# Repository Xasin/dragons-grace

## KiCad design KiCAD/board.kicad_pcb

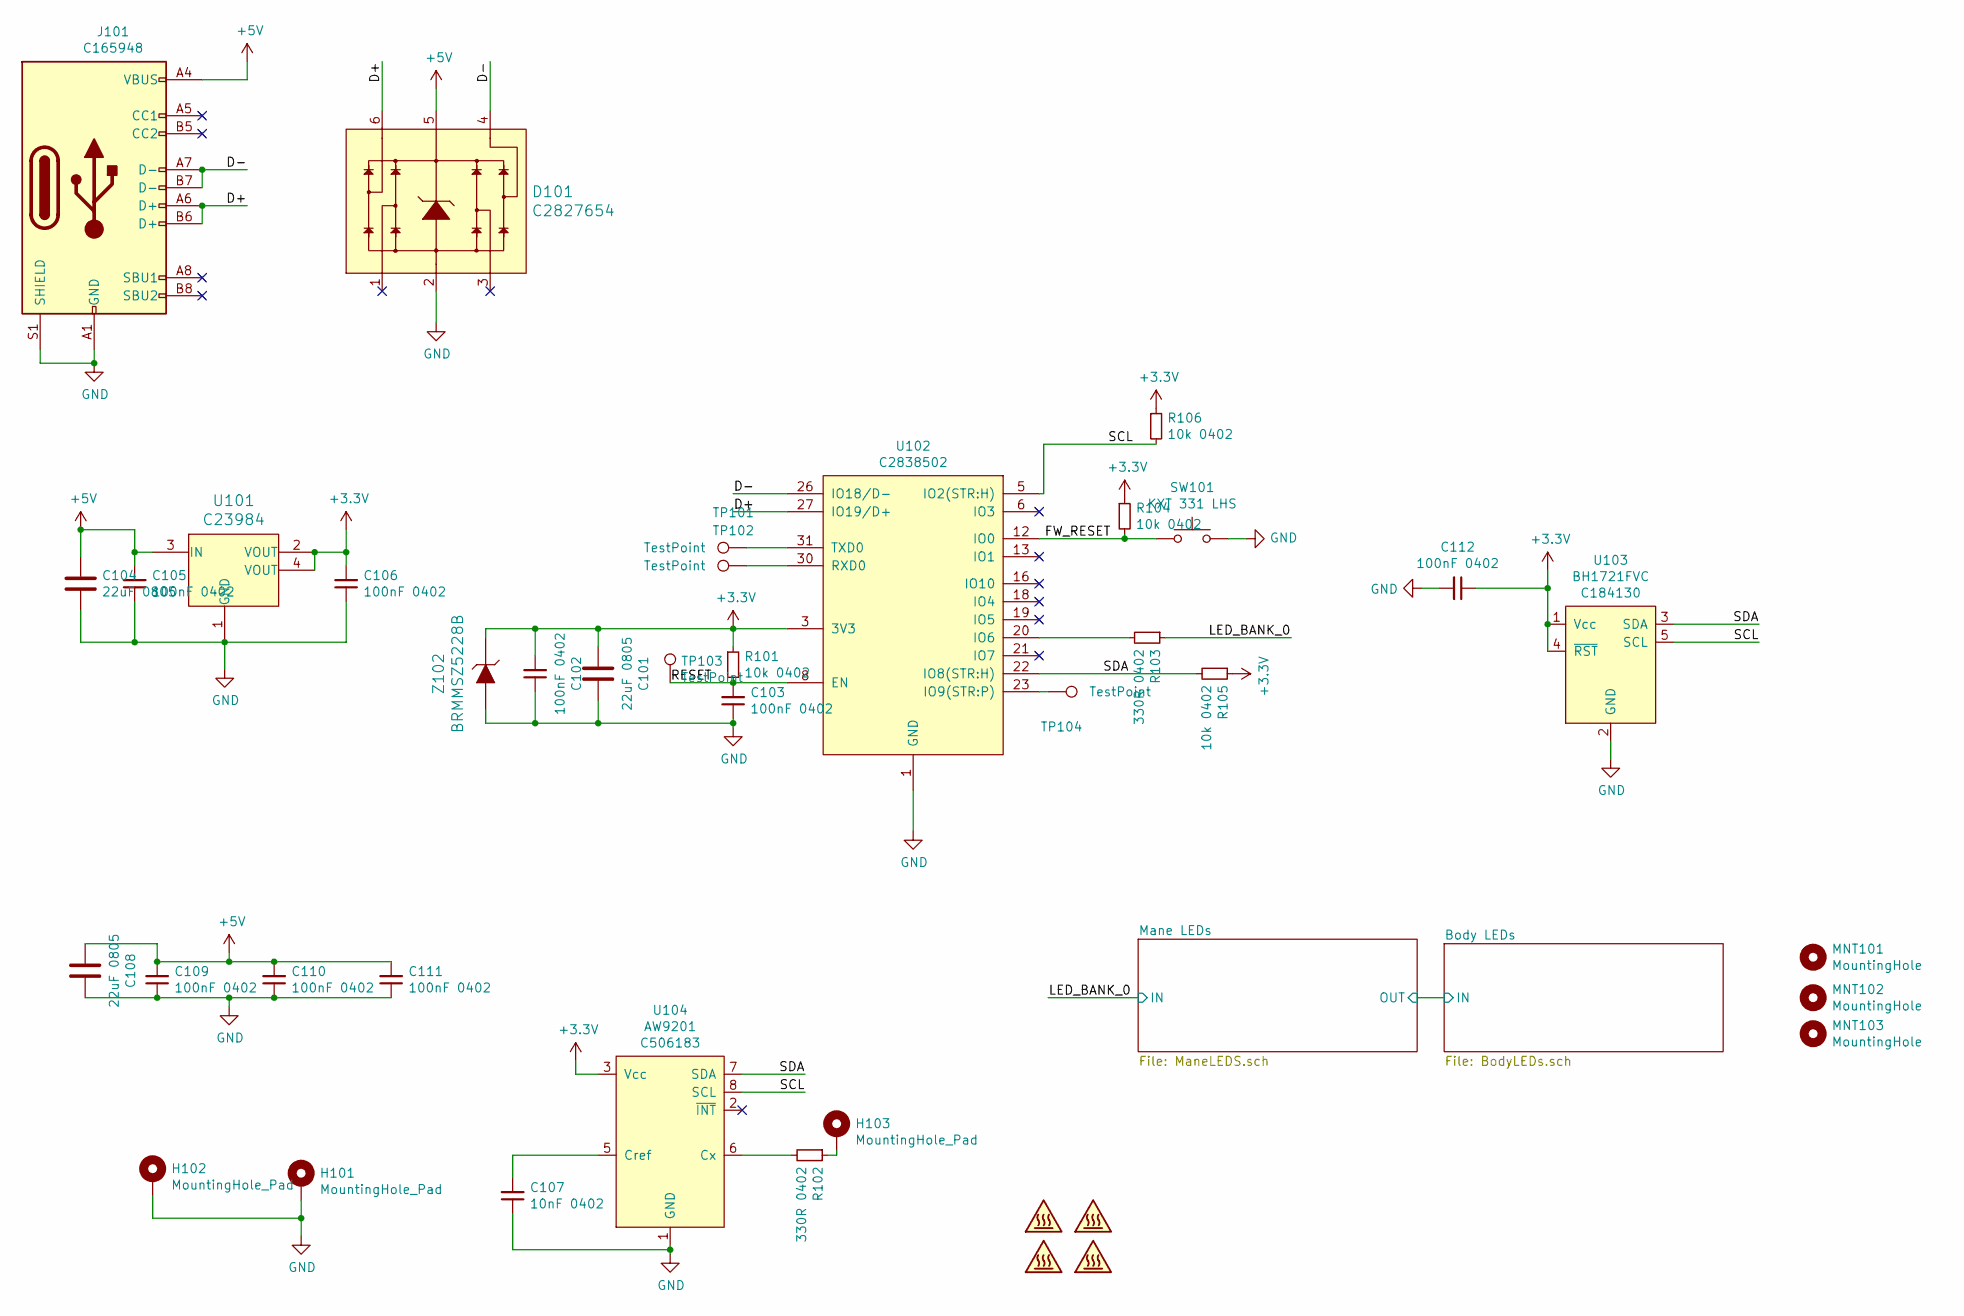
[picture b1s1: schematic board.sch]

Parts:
C101, C104, C108: 22uF 0805; C_0805_2012Metric; JLCPART C45783
C102, C103, C105, C106, C109, C111, C112: 100nF 0402; C_0402_1005Metric; JLCPART C307331
C107: 10nF 0402; C_0402_1005Metric
C110: 100nF 0402; C_0402_1005Metric
D101: C2827654; SOT23-6L; MPN USBLC6-2SC6; Digi-Key_PN 497-5235-1-ND
H101, H102, H103: MountingHole_Pad; MountingHole_1.5mm_M1_Pad_Via
J101: C165948; USB_C_Receptacle_HRO_TYPE-C-31-M-12; JLCPART C165948
MNT101, MNT102, MNT103: MountingHole; JLC_TOOLINGHOLE
R101, R104, R105, R106: 10k 0402; R_0402_1005Metric; JLCPART C25744
R102, R103: 330R 0402; R_0402_1005Metric; JLCPART C226996
SW101: KXT 331 LHS; SW_SPST_CK_KXT3
SYM101: SYM_Hot_Small; dragon-silk
SYM102: SYM_Hot_Small; DragonIcon_7mm_Solder
SYM103: SYM_Hot_Small; config_q
SYM104: SYM_Hot_Small; dragon-silk-back
TP101, TP102, TP103, TP104: TestPoint; TestPoint_Pad_D1.5mm
U101: C23984; SOT-223; MPN AP2114H-3.3TRG1; Digi-Key_PN AP2114H-3.3TRG1DICT-ND
U102: C2838502; ESP32-C3-MINI; JLCPART C2838502
U103: BH1721FVC; WSOF5; JLCPART C184130
U104: AW9201; QFN-8L; JLCPART C506183
Z102: BRMMSZ5228B; SOD-123; MPN DDZ9689-7; Digi-Key_PN DDZ9689DICT-ND

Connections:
+3V3: C101.2, C102.2, C106.2, C112.1, R101.1, R104.1, R105.1, R106.1, U101.2 (VOUT), U101.4 (VOUT), U102.3 (3V3), U103.1 (Vcc), U103.4 (~RST), U104.3 (Vcc), Z102.K
+5V: C104.2, C105.2, C108.2, C109.2, C110.2, C111.2, D101.5, J101.A4 (VBUS), J101.A9 (VBUS), J101.B4 (VBUS), J101.B9 (VBUS), U101.3 (IN); also elsewhere on the board
/D+: D101.6, J101.A6 (D+), J101.B6 (D+), U102.27 (IO19/D+)
/D-: D101.4, J101.A7 (D-), J101.B7 (D-), U102.26 (IO18/D-)
/FW_RESET: R104.2, SW101.1, U102.12 (IO0)
/LED_BANK_0: R103.1; also elsewhere on the board
/RESET: C103.2, R101.2, TP103.1, U102.8 (EN)
/SCL: R106.2, U102.5 (IO2(STR:H)), U103.5 (SCL), U104.8 (SCL)
/SDA: R105.2, U102.22 (IO8(STR:H)), U103.3 (SDA), U104.7 (SDA)
GND: C101.1, C102.1, C103.1, C104.1, C105.1, C106.1, C107.1, C108.1, C109.1, C110.1, C111.1, C112.2, D101.2, H101.1, H102.1, J101.A1 (GND), J101.A12 (GND), J101.B1 (GND), J101.B12 (GND), J101.S1 (SHIELD), SW101.2, U101.1 (GND), U102.1 (GND), U103.2 (GND), U104.1 (GND), Z102.A; also elsewhere on the board
unnamed: C107.2, U104.5 (Cref)
unnamed: H103.1, R102.1
unnamed: R102.2, U104.6 (Cx)
unnamed: R103.2, U102.20 (IO6)
unnamed: TP101.1, U102.31 (TXD0)
unnamed: TP102.1, U102.30 (RXD0)
unnamed: TP104.1, U102.23 (IO9(STR:P))

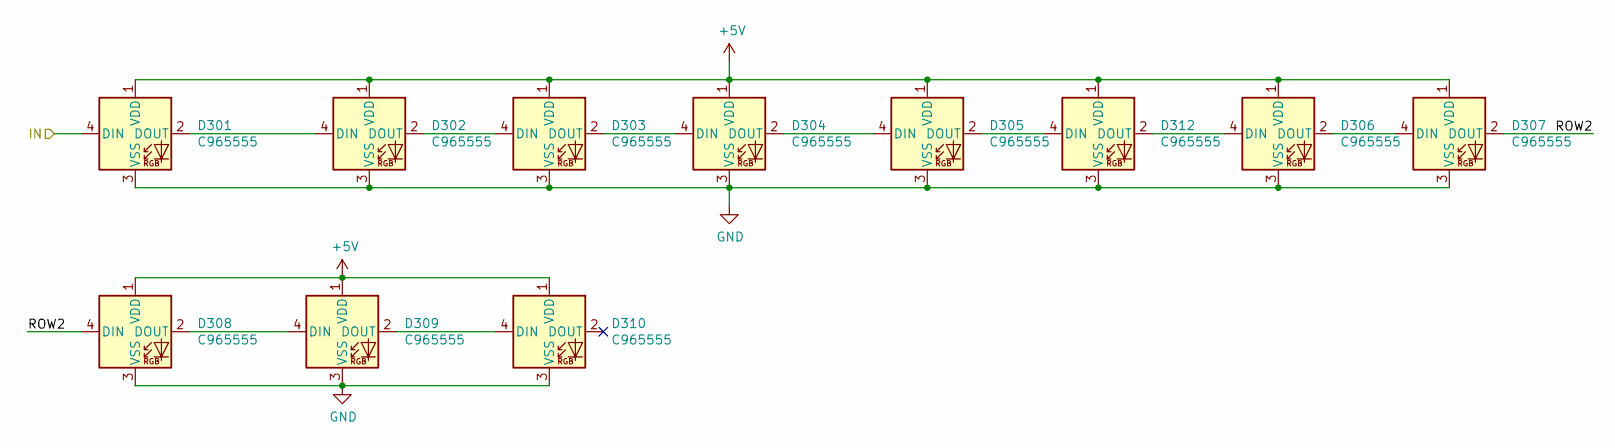
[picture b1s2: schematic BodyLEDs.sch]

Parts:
D301, D302, D303, D304, D305, D306, D307, D308, D309, D310, D312: C965555; WS2812B-2020; JLCPART C965555

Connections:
+5V: D301.1 (VDD), D302.1 (VDD), D303.1 (VDD), D304.1 (VDD), D305.1 (VDD), D306.1 (VDD), D307.1 (VDD), D308.1 (VDD), D309.1 (VDD), D310.1 (VDD), D312.1 (VDD); also elsewhere on the board
/Body LEDs/IN: D301.4 (DIN); also elsewhere on the board
/Body LEDs/ROW2: D307.2 (DOUT), D308.4 (DIN)
GND: D301.3 (VSS), D302.3 (VSS), D303.3 (VSS), D304.3 (VSS), D305.3 (VSS), D306.3 (VSS), D307.3 (VSS), D308.3 (VSS), D309.3 (VSS), D310.3 (VSS), D312.3 (VSS); also elsewhere on the board
unnamed: D301.2 (DOUT), D302.4 (DIN)
unnamed: D302.2 (DOUT), D303.4 (DIN)
unnamed: D303.2 (DOUT), D304.4 (DIN)
unnamed: D304.2 (DOUT), D305.4 (DIN)
unnamed: D305.2 (DOUT), D312.4 (DIN)
unnamed: D306.2 (DOUT), D307.4 (DIN)
unnamed: D306.4 (DIN), D312.2 (DOUT)
unnamed: D308.2 (DOUT), D309.4 (DIN)
unnamed: D309.2 (DOUT), D310.4 (DIN)

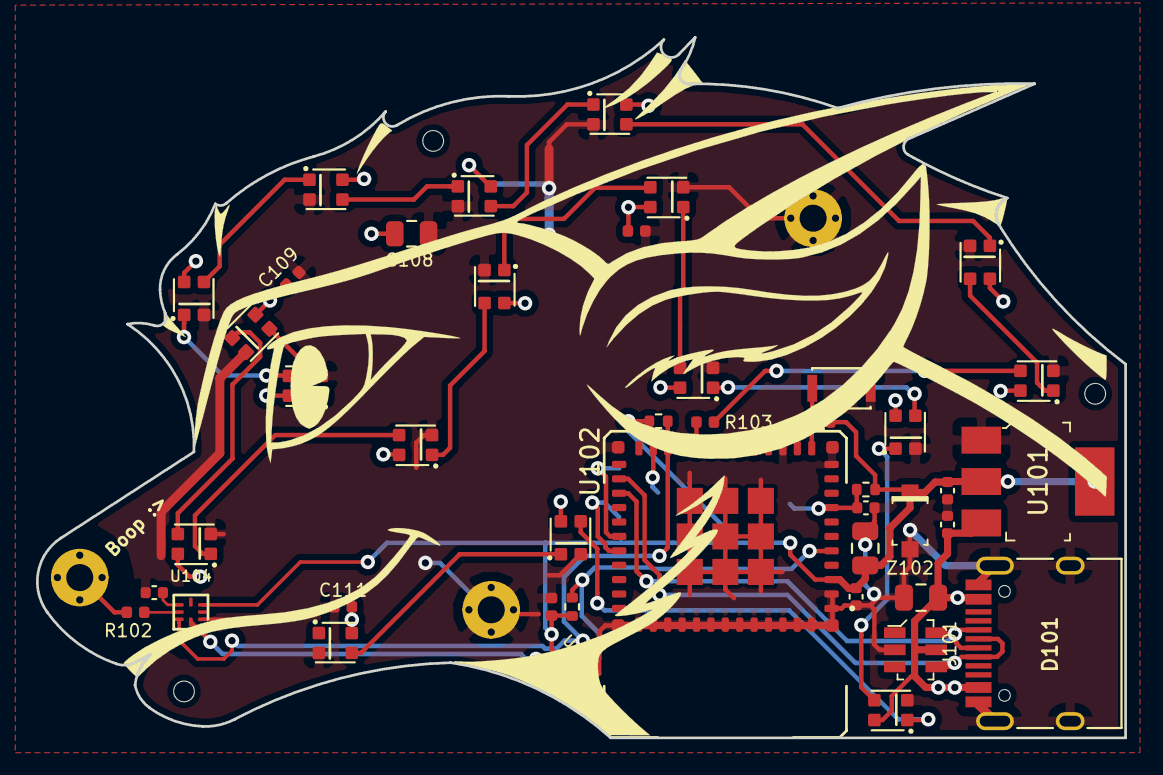
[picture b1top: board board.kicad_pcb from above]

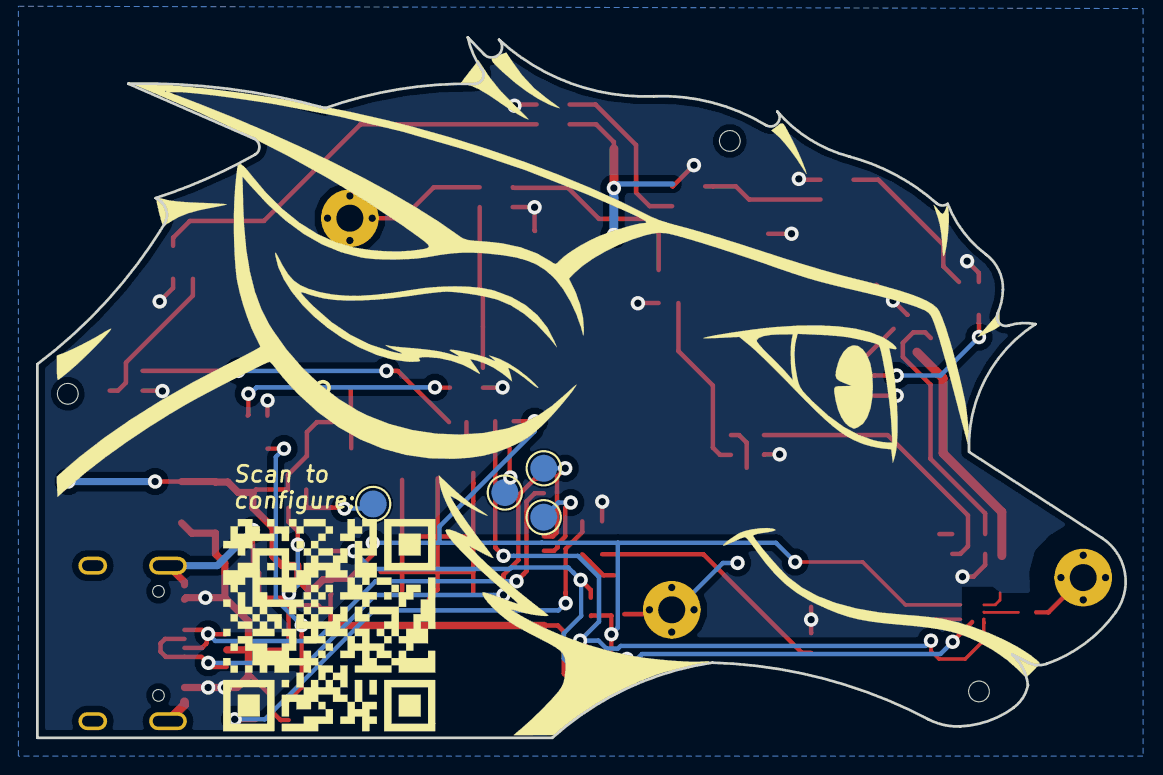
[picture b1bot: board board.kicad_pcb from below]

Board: 2 copper layers, 60.5 x 38.9 mm, 57 parts (6 on the bottom side), 33 nets.

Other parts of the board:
D201, D202, D203, D204, D205, D206: C965555; WS2812B-2020

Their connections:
+5V: D201.1, D202.1, D203.1, D204.1, D205.1, D206.1; also elsewhere on the board
/Body LEDs/IN: D206.2; also elsewhere on the board
/LED_BANK_0: D201.4; also elsewhere on the board
/Mane LEDs/ROW_2: D205.2, D206.4
GND: D201.3, D202.3, D203.3, D204.3, D205.3, D206.3; also elsewhere on the board
unnamed: D201.2, D202.4
unnamed: D202.2, D203.4
unnamed: D203.2, D204.4
unnamed: D204.2, D205.4

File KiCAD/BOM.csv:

"Id";"Designator";"Package";"Quantity";"Designation";"Supplier and ref";
1;"R104,R101";"R_0402_1005Metric";2;"10k 0402";;;
2;"C113,C112,C111,C110,C109,C106,C105,C103,C102";"C_0402_1005Metric";9;"0.1uF 0402";;;
3;"SW101";"SW_SPST_CK_KXT3";1;"KXT 331 LHS";;;
4;"U103";"Ambient_Prox_APDS-9960";1;"APDS-9960";;;
5;"R103,R102";"R_0402_1005Metric";2;"330R 0402";;;
6;"C108,C101,C104";"C_0805_2012Metric";3;"22uF 0805";;;
7;"J102";"SOIC_clipProgSmall";1;"Conn_02x04_Counter_Clockwise";;;
8;"C107";"C_0402_1005Metric";1;"0.8pF 0402";;;
9;"L101";"L_0402_1005Metric";1;"5.6nH 0402";;;
10;"AE101";"Johanson_2450AT43F0100";1;"2450AT43F0100";;;
11;"D312,D310,D309,D308,D302,D307,D306,D305,D304,D303,D301,D207,D205,D206,D204,D202,D201,D203";"SMD-LX0707RGB-TR";18;"LX0707RGB";;;
12;"SYM101";"dragon-silk";1;"SYM_Hot_Small";;;
13;"H102,H103,H101";"MountingHole_1.5mm_M1_Pad_Via";3;"MountingHole_Pad";;;
14;"J101";"USB_C_Receptacle_HRO_TYPE-C-31-M-12";1;"USB4105-GF-A";;;
15;"U102";"QFN-48-1EP_7x7mm_P0.5mm_EP5.3x5.3mm";1;"ESP32-PICO-D4";;;
16;"Z102";"SOD-123";1;"DDZ9685";;;
17;"Z101";"SOD-123";1;"DDZ9690";;;
18;"U101";"SOT-223";1;"AP2114H-3_3TRG1";;;

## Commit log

2021-10-15 Add first bits of code
2021-10-15 Bump XasCode version
2021-12-03 Add FreeCAD and KiCAD source files
2021-12-03 Add extra outlines etc.
2021-12-03 Add XNM OTA configuration
2021-12-03 Bump XasCode
2022-01-01 Polish up ESP32 code
2022-01-01 Add website for Rainbow's viewing (dis)pleasure
